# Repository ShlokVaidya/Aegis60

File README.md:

# Aegis60
Aegis60 is my custom 60% mechanical keyboard project built around an RP2040-ZERO controller.
<p>
I wanted a keyboard that felt clean and simple like a classic 60%, but still let me fully understand how the electronics actually work (matrix, diodes, routing, and firmware pin mapping), not just buy a kit and screw it together.
</p>
<br>

<br>
## Why I made this

I am 17 and I use my keyboard for school every day, so I wanted to build one that is actually mine from scratch.

Main goals I set for myself:
- Design a full 60% PCB in KiCad (61 keys)
- Use hot-swap MX footprints so it is easy to test switches
- Keep the design manufacturable and not just a concept render
- Learn the full pipeline: schematic -> PCB -> 3D model -> production files

## Project status

This repo includes the complete hardware design files and manufacturing outputs:
- KiCad project, schematic, and PCB
- 3D CAD export (.step)
- Plate DXF
- Production files (BOM, positions, designators, netlist)
- Custom RP2040-ZERO symbol/footprint library files

Current hardware summary:
- Layout: 60% ANSI style, 61 keys
- Controller: RP2040-ZERO
- Matrix: diode matrix (1 diode per switch)
- Stabilizers: 2u, 2.25u, 2.75u, 6.25u support

## Images

### Full 3D model screenshot

### PCB screenshot

### Wiring / schematic screenshot

### Other Screenshots

### Build

## Repo file checklist

Important files in this repository:
- `Aegis60.kicad_pro`
- `Aegis60.kicad_sch`
- `Aegis60.kicad_pcb`
- `Aegis60.step`
- `Plate.dxf`
- `bom.csv`
- `production/bom.csv`
- `production/positions.csv`
- `production/designators.csv`
- `production/netlist.ipc`

## CAD

OnShape: [link](https://cad.onshape.com/documents/3631dcb843d220359551c32b/w/64ccd39e08fb4eede3b1f39f/e/fad0ee0c4f93314d35213121)

## Firmware note

A KMK starter firmware is included in this repo:

- `firmware/kmk/main.py`
- `firmware/kmk/README.md`

It includes the row/column pin mapping from the current netlist and a base ANSI-like 61-key layout.

## BOM (summary)

Current BOM is in `bom.csv`.

| Name | Purpose | Quantity | Total Cost (USD) | Distributor | Link |
|---|---|---:|---:|---|---|
| 3D printed Case | 3D printing | 1 | 8.19 | Hack Club | https://printlegion.hackclub.com |
| PCB fabrication | PCB | 1 | 39.20 | Robu.in | https://robu.in/product/online-pcb-manufacturing-service/ |
| RP2040-zero | Microcontroller | 1 | 6.05 | Robu.in | https://robu.in/product/waveshare-rp2040-zero-raspberry-pi-mcu-with-presoldered-header/ |
| Cherry PBT Keycaps | Keycaps | 1 | 17.47 | Curiosity Caps | https://curiositycaps.in/products/counter-strike-printstream-decal-collectio-n-cherry-pbt-keycaps |
| Durock Smokey Screw-In Stabilizers V2 | Stabilizers | 1 | 17.00 | StacksKB | https://stackskb.com/store/durock-smokey-screw-in-stabilizers-v2/ |
| Akko V5 Creamy Blue Pro Switch (Pack of 45) | For typing I guess ? | 1 | 13.14 | StacksKB | https://stackskb.com/store/akko-v5-creamy-blue-pro-switch-pack-of-45/ |

**Total BOM cost:** 101.05 USD

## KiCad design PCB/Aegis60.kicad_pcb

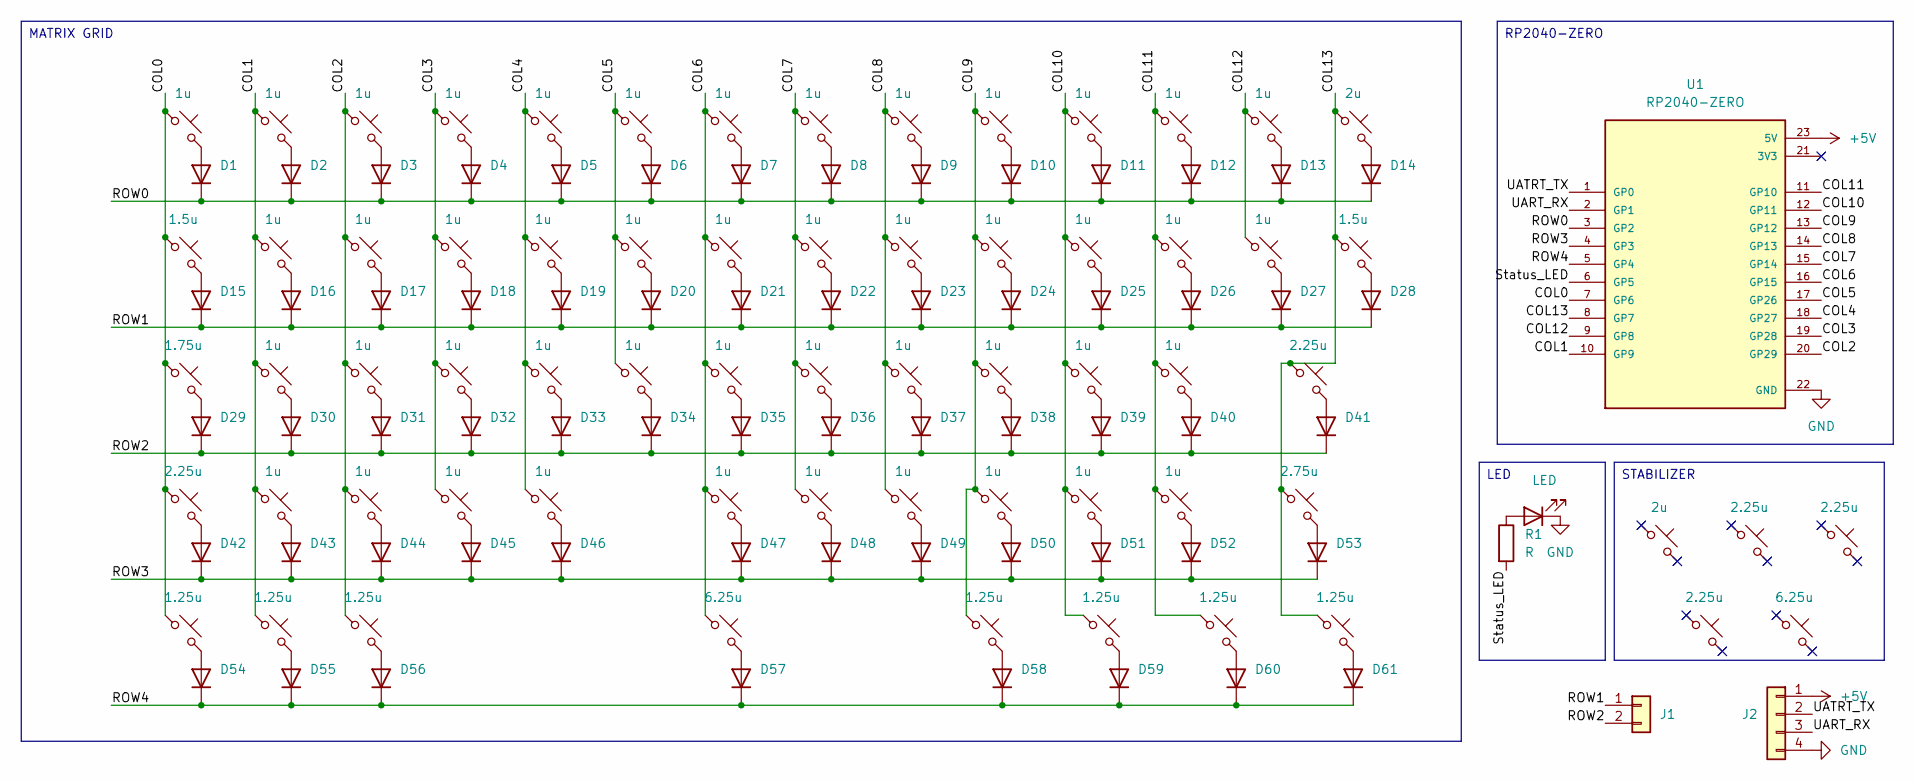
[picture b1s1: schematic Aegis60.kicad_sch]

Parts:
D1, D2, D3, D4, D5, D6, D7, D8, D9, D10, D11, D12, D13, D14, D15, D16, D17, D18, D19, D20, D21, D22, D23, D24, D25, D26, D27, D28, D29, D30, D31, D32, D33, D34, D35, D36, D37, D38, D39, D40, D41, D42, D43, D44, D45, D46, D47, D48, D49, D50, D51, D52, D53, D54, D55, D56, D57, D58, D59, D60, D61: 1N4148; D_DO-35_SOD27_P7.62mm_Horizontal
D62: LED; LED_1206_3216Metric_Pad1.42x1.75mm_HandSolder
J1: Conn_01x02; PinSocket_1x02_P2.54mm_Vertical
J2: Conn_01x04; PinHeader_1x04_P2.54mm_Horizontal
R1: R; R_1206_3216Metric
STAB1: 2u; STAB_MX_2u
STAB2, STAB3: 2.25u; STAB_MX_2.25u
STAB4: 2.25u; STAB_MX_2.75u
STAB5: 6.25u; STAB_MX_6.25u
SW1, SW2, SW3, SW4, SW5, SW6, SW7, SW8, SW9, SW10, SW11, SW12, SW13, SW16, SW17, SW18, SW19, SW20, SW21, SW22, SW23, SW24, SW25, SW26, SW27, SW30, SW31, SW32, SW33, SW34, SW35, SW36, SW37, SW38, SW39, SW40, SW43, SW44, SW45, SW46, SW47, SW48, SW49, SW50, SW51, SW52: 1u; SW_MX_HS_KS-2P02B01-01_1u
SW14: 2u; SW_MX_HS_KS-2P02B01-01_1u
SW15, SW28: 1.5u; SW_MX_HS_KS-2P02B01-01_1.5u
SW29: 1.75u; SW_MX_HS_KS-2P02B01-01_1.75u
SW41, SW42: 2.25u; SW_MX_HS_KS-2P02B01-01_1u
SW53: 2.75u; SW_MX_HS_KS-2P02B01-01_1u
SW54, SW55, SW56, SW58, SW59, SW60, SW61: 1.25u; SW_MX_HS_KS-2P02B01-01_1.25u
SW57: 6.25u; SW_MX_HS_KS-2P02B01-01_1u
U1: RP2040-ZERO; MODULE_RP2040-ZERO; PARTREV NA

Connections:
+5V: J2.1, U1.23 (5V)
/COL0: SW1.1, SW15.1, SW29.1, SW42.1, SW54.1, U1.7 (GP6)
/COL1: SW2.1, SW16.1, SW30.1, SW43.1, SW55.1, U1.10 (GP9)
/COL2: SW3.1, SW17.1, SW31.1, SW44.1, SW56.1, U1.20 (GP29)
/COL3: SW4.1, SW18.1, SW32.1, SW45.1, U1.19 (GP28)
/COL4: SW5.1, SW19.1, SW33.1, SW46.1, U1.18 (GP27)
/COL5: SW6.1, SW20.1, SW34.1, U1.17 (GP26)
/COL6: SW7.1, SW21.1, SW35.1, SW47.1, SW57.1, U1.16 (GP15)
/COL7: SW8.1, SW22.1, SW36.1, SW48.1, U1.15 (GP14)
/COL8: SW9.1, SW23.1, SW37.1, SW49.1, U1.14 (GP13)
/COL9: SW10.1, SW24.1, SW38.1, SW50.1, SW58.1, U1.13 (GP12)
/COL10: SW11.1, SW25.1, SW39.1, SW51.1, SW59.1, U1.12 (GP11)
/COL11: SW12.1, SW26.1, SW40.1, SW52.1, SW60.1, U1.11 (GP10)
/COL12: SW13.1, SW27.1, U1.9 (GP8)
/COL13: SW14.1, SW28.1, SW41.1, SW53.1, SW61.1, U1.8 (GP7)
/ROW0: D1.1 (K), D2.1 (K), D3.1 (K), D4.1 (K), D5.1 (K), D6.1 (K), D7.1 (K), D8.1 (K), D9.1 (K), D10.1 (K), D11.1 (K), D12.1 (K), D13.1 (K), D14.1 (K), U1.3 (GP2)
/ROW1: D15.1 (K), D16.1 (K), D17.1 (K), D18.1 (K), D19.1 (K), D20.1 (K), D21.1 (K), D22.1 (K), D23.1 (K), D24.1 (K), D25.1 (K), D26.1 (K), D27.1 (K), D28.1 (K), J1.1
/ROW2: D29.1 (K), D30.1 (K), D31.1 (K), D32.1 (K), D33.1 (K), D34.1 (K), D35.1 (K), D36.1 (K), D37.1 (K), D38.1 (K), D39.1 (K), D40.1 (K), D41.1 (K), J1.2
/ROW3: D42.1 (K), D43.1 (K), D44.1 (K), D45.1 (K), D46.1 (K), D47.1 (K), D48.1 (K), D49.1 (K), D50.1 (K), D51.1 (K), D52.1 (K), D53.1 (K), U1.4 (GP3)
/ROW4: D54.1 (K), D55.1 (K), D56.1 (K), D57.1 (K), D58.1 (K), D59.1 (K), D60.1 (K), D61.1 (K), U1.5 (GP4)
/Status_LED: R1.2, U1.6 (GP5)
/UART_RX: J2.3, U1.2 (GP1)
/UATRT_TX: J2.2, U1.1 (GP0)
GND: D62.1 (K), J2.4, U1.22 (GND)
unnamed: D1.2 (A), SW1.2
unnamed: D2.2 (A), SW2.2
unnamed: D3.2 (A), SW3.2
unnamed: D4.2 (A), SW4.2
unnamed: D5.2 (A), SW5.2
unnamed: D6.2 (A), SW6.2
unnamed: D7.2 (A), SW7.2
unnamed: D8.2 (A), SW8.2
unnamed: D9.2 (A), SW9.2
unnamed: D10.2 (A), SW10.2
unnamed: D11.2 (A), SW11.2
unnamed: D12.2 (A), SW12.2
unnamed: D13.2 (A), SW13.2
unnamed: D14.2 (A), SW14.2
unnamed: D15.2 (A), SW15.2
unnamed: D16.2 (A), SW16.2
unnamed: D17.2 (A), SW17.2
unnamed: D18.2 (A), SW18.2
unnamed: D19.2 (A), SW19.2
unnamed: D20.2 (A), SW20.2
unnamed: D21.2 (A), SW21.2
unnamed: D22.2 (A), SW22.2
unnamed: D23.2 (A), SW23.2
unnamed: D24.2 (A), SW24.2
unnamed: D25.2 (A), SW25.2
unnamed: D26.2 (A), SW26.2
unnamed: D27.2 (A), SW27.2
unnamed: D28.2 (A), SW28.2
unnamed: D29.2 (A), SW29.2
unnamed: D30.2 (A), SW30.2
unnamed: D31.2 (A), SW31.2
unnamed: D32.2 (A), SW32.2
unnamed: D33.2 (A), SW33.2
unnamed: D34.2 (A), SW34.2
unnamed: D35.2 (A), SW35.2
unnamed: D36.2 (A), SW36.2
unnamed: D37.2 (A), SW37.2
unnamed: D38.2 (A), SW38.2
unnamed: D39.2 (A), SW39.2
unnamed: D40.2 (A), SW40.2
unnamed: D41.2 (A), SW41.2
unnamed: D42.2 (A), SW42.2
unnamed: D43.2 (A), SW43.2
unnamed: D44.2 (A), SW44.2
unnamed: D45.2 (A), SW45.2
unnamed: D46.2 (A), SW46.2
unnamed: D47.2 (A), SW47.2
unnamed: D48.2 (A), SW48.2
unnamed: D49.2 (A), SW49.2
unnamed: D50.2 (A), SW50.2
unnamed: D51.2 (A), SW51.2
unnamed: D52.2 (A), SW52.2
unnamed: D53.2 (A), SW53.2
unnamed: D54.2 (A), SW54.2
unnamed: D55.2 (A), SW55.2
unnamed: D56.2 (A), SW56.2
unnamed: D57.2 (A), SW57.2
unnamed: D58.2 (A), SW58.2
unnamed: D59.2 (A), SW59.2
unnamed: D60.2 (A), SW60.2
unnamed: D61.2 (A), SW61.2
unnamed: D62.2 (A), R1.1

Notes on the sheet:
STABILIZER
RP2040-ZERO
LED
MATRIX GRID

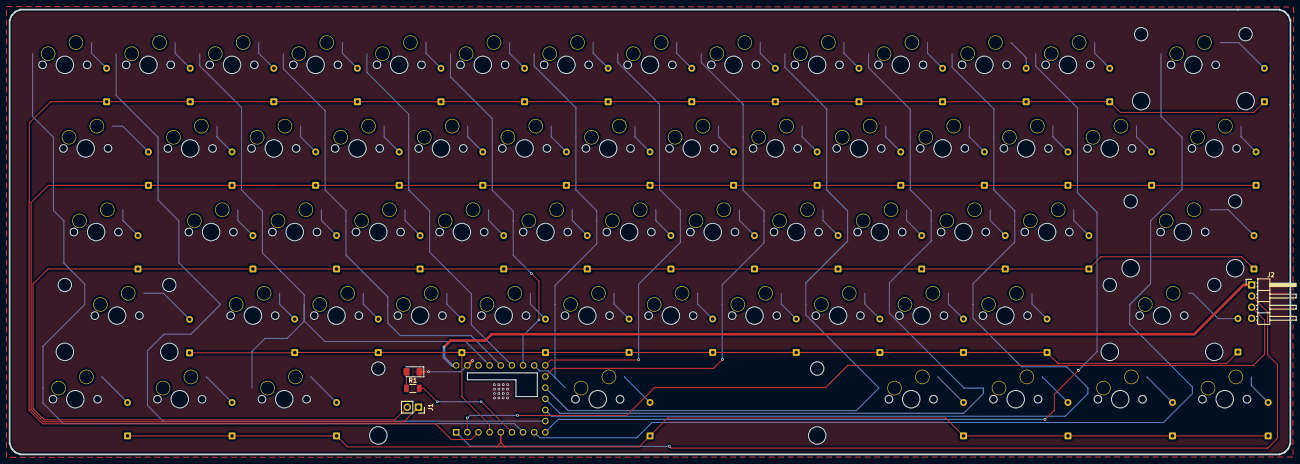
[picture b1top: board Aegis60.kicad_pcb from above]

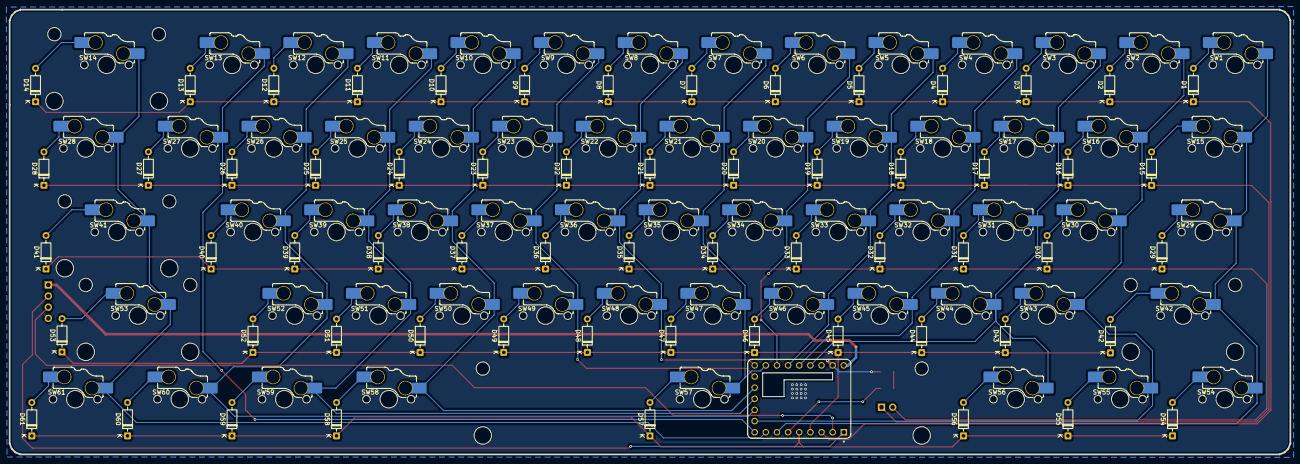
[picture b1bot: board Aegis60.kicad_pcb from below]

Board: 2 copper layers, 291.9 x 101.4 mm, 132 parts (123 on the bottom side), 86 nets.

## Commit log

2026-03-22 revised v2.2
2026-03-22 revised v2.3
2026-03-22 revised v2.4
2026-05-21 build
